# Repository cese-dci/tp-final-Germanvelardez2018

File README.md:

## Trabajo práctico final de la asignatura DCI ##
Este repositorio contiene el trabajo práctico final para la asignatura de Diseño de Circuitos Impresos de la carrera de posgrado de FIUBA.

* Autor: German Gabriel Velardez
* Título corto del trabajo:  Replica de modulo de comunicacion basado en el chip SIM7000G
* Descripción:  Modulo de comunicacion basado GSM/4G con GNSS incluido.

## Licencia de este trabajo ##
La licencia utilizada en este proyecto es : <b>CERN Open Hardware Licence Version 2</b>. 

## Estructura del TP FINAL ##

Se repositorio esta estructurado de la siguiente manera.

* doc: Toda la información sobre el circuito, principalmente de autoría o procesamiento propio. 
* info: Toda la iformación recolectada sobre el circuito, como por ejemplo:
  * Hojas de datos.
  * Info de productos comerciales.
  * Info en internet.
* pcb: Archivos de diseño esquemático y pcb.

## Replica de modulo de comunicacion basado en SIM7000
# Diseño final

 ### Dimensiones del nuevo modulo:
  <ul>
    <li>
     Largo: 80 mm
    </li>  
    <li>
    Ancho: 60 mm
    </li> 
  </lu> 

  ### Primera tentativa de posicionamiento de elementos

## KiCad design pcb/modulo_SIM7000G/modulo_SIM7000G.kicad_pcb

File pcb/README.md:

## Archivos Kicad ##
Este directorio contiene 2 carpetas:
<ul>
  <li>[lib] Librerias de componentes y modelos 3D</li>
  <li>[modulo_SIM7000G] Carpeta del proyecto KICAD</li>
  <ul>

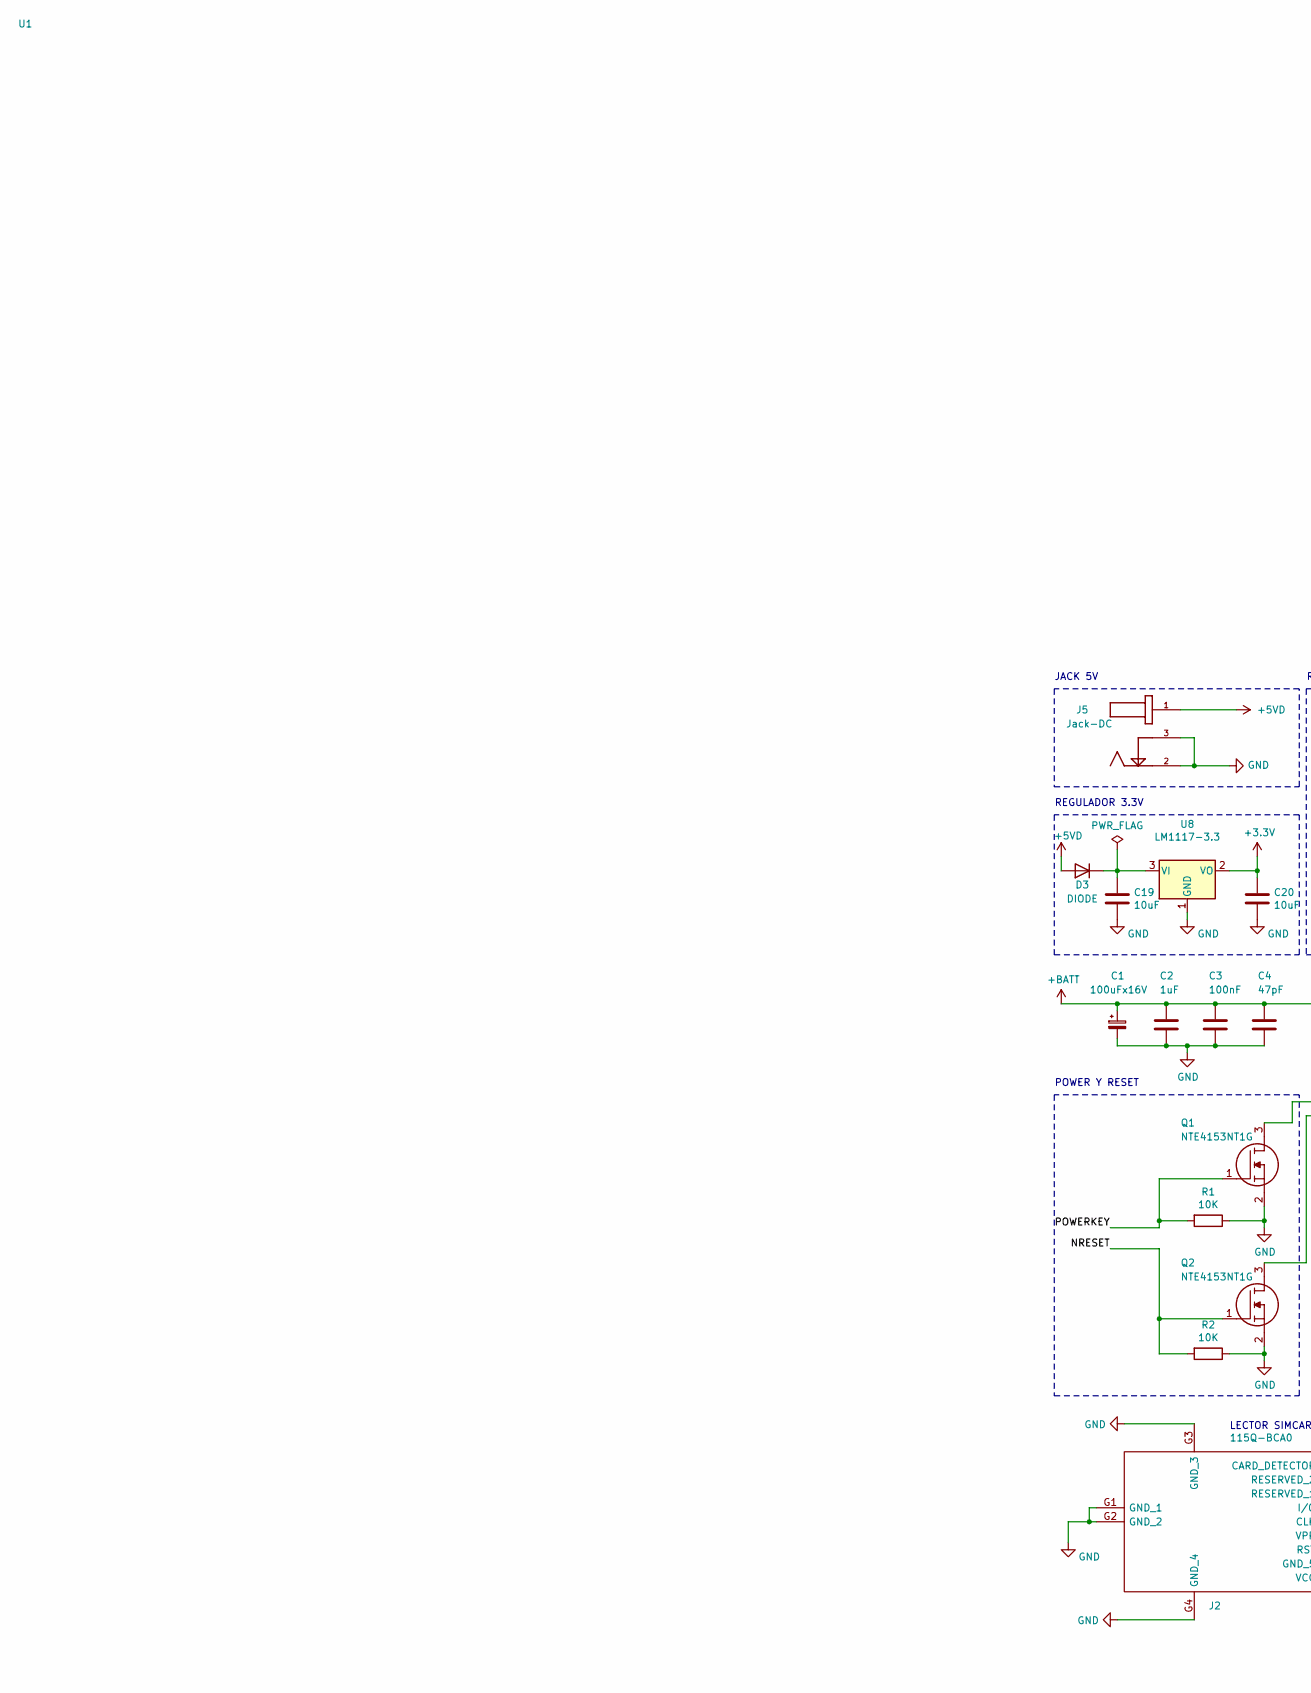
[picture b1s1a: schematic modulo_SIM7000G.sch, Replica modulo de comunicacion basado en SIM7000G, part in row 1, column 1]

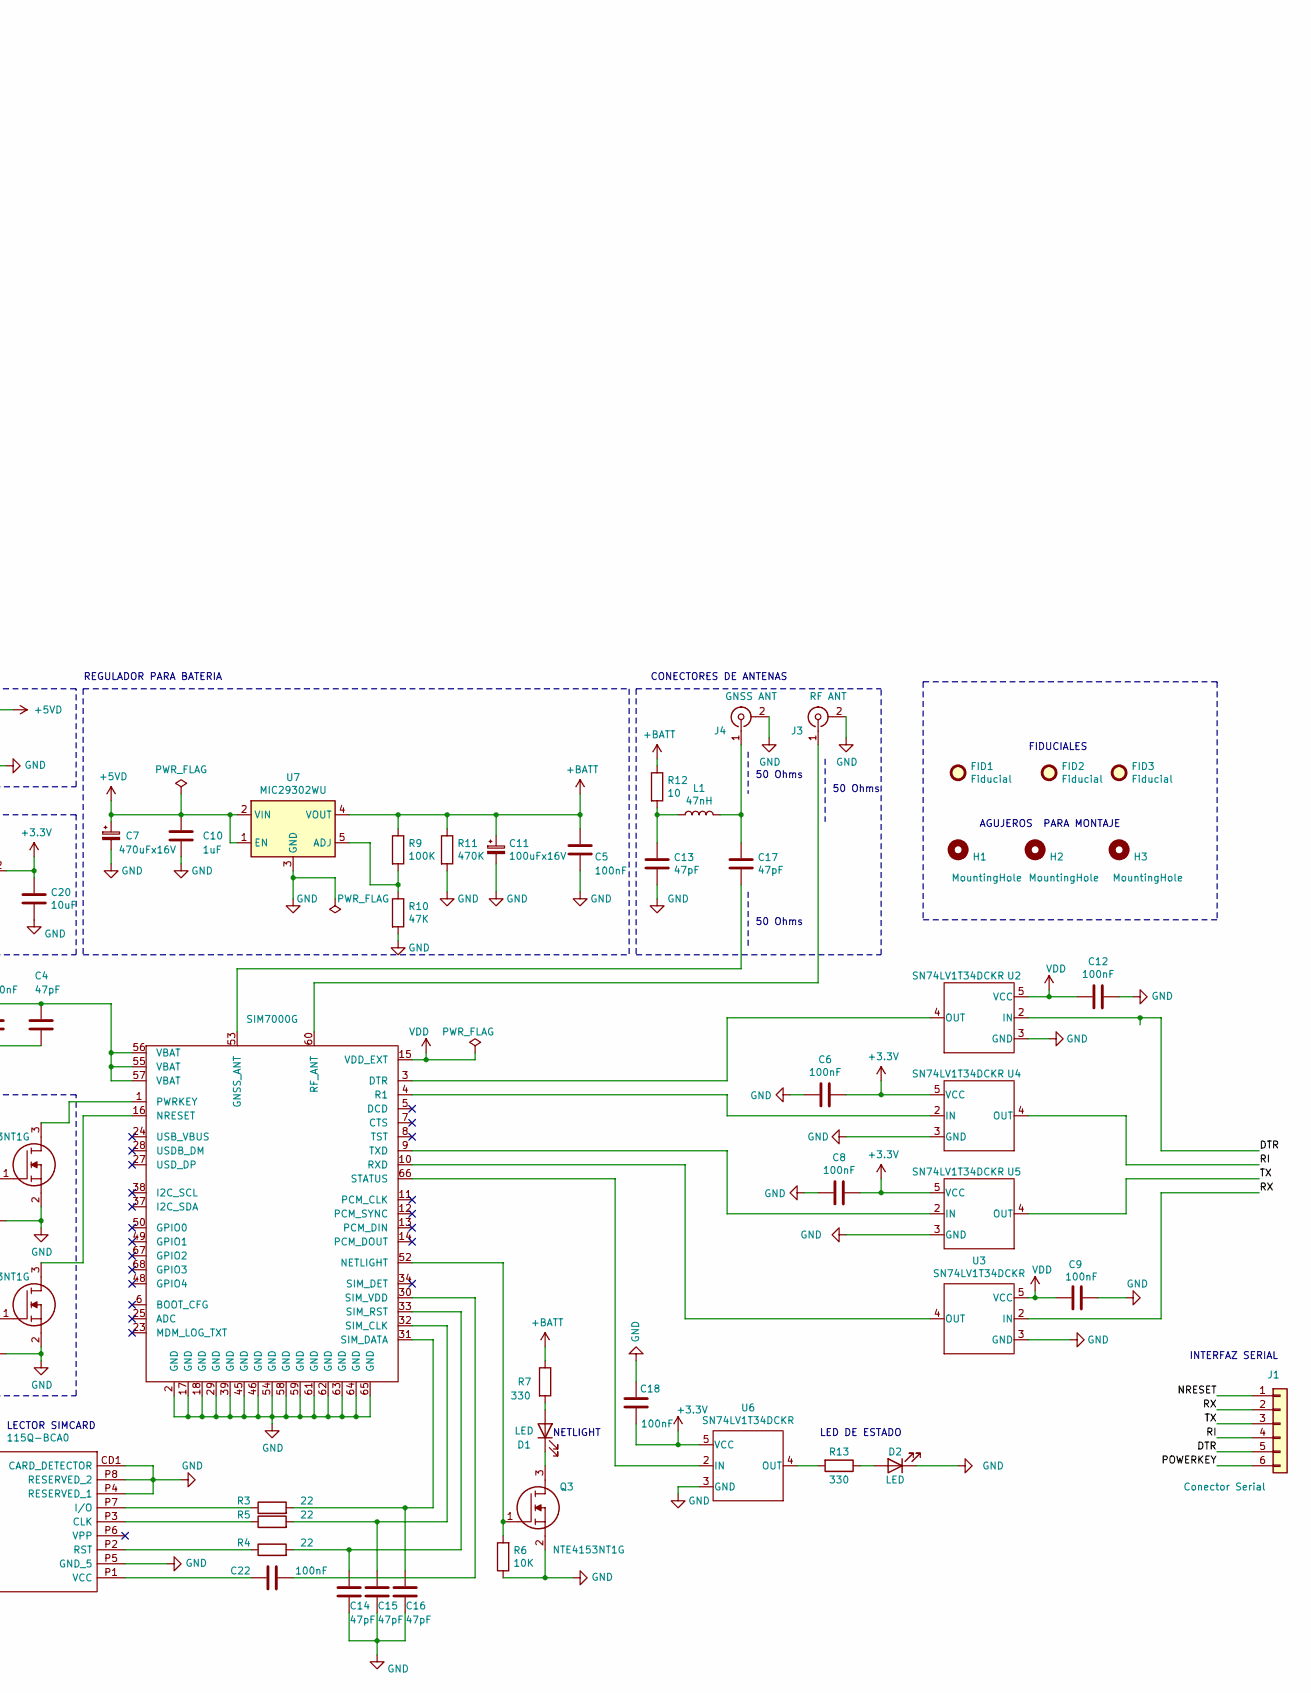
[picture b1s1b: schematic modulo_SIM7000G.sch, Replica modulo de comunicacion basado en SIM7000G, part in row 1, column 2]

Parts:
C1, C11: 100uFx16V; CP_Elec_6.3x9.9
C2, C10: 1uF; C_0805_2012Metric_Pad1.18x1.45mm_HandSolder
C3, C5, C6, C8, C9, C12, C18, C22: 100nF; C_0805_2012Metric_Pad1.18x1.45mm_HandSolder
C4, C13, C14, C15, C16, C17: 47pF; C_0805_2012Metric_Pad1.18x1.45mm_HandSolder
C7: 470uFx16V; CP_Elec_8x10
C19, C20: 10uF; C_0805_2012Metric_Pad1.18x1.45mm_HandSolder
D1, D2: LED; LED_0805_2012Metric
D3: DIODE; D_0805_2012Metric_Pad1.15x1.40mm_HandSolder
FID1, FID2, FID3: Fiducial; Fiducial_1mm_Mask2mm
H1, H2, H3: MountingHole; MountingHole_2.2mm_M2_ISO7380_Pad_TopBottom
J1: Conector Serial; PinHeader_1x06_P2.54mm_Horizontal
J2: 115Q-BCA0; 115QBCA0; Manufacturer_Part_Number 115Q-BCA0
J3: RF ANT; SMA_Amphenol_132203-12_Horizontal
J4: GNSS ANT; SMA_Amphenol_132203-12_Horizontal
J5: Jack-DC; BarrelJack_CUI_PJ-063AH_Horizontal
L1: 47nH; L_0805_2012Metric
Q1, Q2, Q3: NTE4153NT1G; SOT-416; Manufacturer_Part_Number NTE4153NT1G; Mouser Part Number 863-NTE4153NT1G
R1, R2, R6: 10K; R_0805_2012Metric
R3, R4, R5: 22; R_0805_2012Metric
R7, R13: 330; R_0805_2012Metric
R9: 100K; R_0805_2012Metric
R10: 47K; R_0805_2012Metric
R11: 470K; R_0805_2012Metric
R12: 10; R_0805_2012Metric
U1: SIM7000G; SIM7000
U2, U3, U4, U5, U6: SN74LV1T34DCKR; SOT-23-5
U7: MIC29302WU; TO-263-5_TabPin3; Digikey 576-1125-2-NDTR
U8: LM1117-3.3; SOT-223

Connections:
+3V3: C6.2, C8.2, C18.1, C20.1, U4.5 (VCC), U5.5 (VCC), U6.5 (VCC), U8.2 (VO)
+5VD: C7.1, C10.1, D3.1 (A), J5.1, U7.1 (EN), U7.2 (VIN)
+BATT: C1.1, C2.1, C3.1, C4.1, C5.1, C11.1, R7.1, R9.1, R11.1, R12.1, U1.55 (VBAT), U1.56 (VBAT), U1.57 (VBAT), U7.4 (VOUT)
/DTR: J1.5, U2.2 (IN)
/NRESET: J1.1, Q2.1, R2.2
/POWERKEY: J1.6, Q1.1, R1.2
/RI: J1.4, U4.4 (OUT)
/RX: J1.2, U3.2 (IN)
/TX: J1.3, U5.4 (OUT)
GND: C1.2, C2.2, C3.2, C4.2, C5.2, C6.1, C7.2, C8.1, C9.2, C10.2, C11.2, C12.2, C13.2, C14.2, C15.2, C16.2, C18.2, C19.2, C20.2, D2.1 (K), J2.CD1 (CARD_DETECTOR), J2.G1 (GND_1), J2.G2 (GND_2), J2.G3 (GND_3), J2.G4 (GND_4), J2.P4 (RESERVED_1), J2.P5 (GND_5), J2.P8 (RESERVED_2), J3.2 (Ext), J4.2 (Ext), J5.2, J5.3, Q1.2, Q2.2, Q3.2, R1.1, R2.1, R6.1, R10.2, R11.2, U1.2 (GND), U1.17 (GND), U1.18 (GND), U1.29 (GND), U1.39 (GND), U1.45 (GND), U1.46 (GND), U1.54 (GND), U1.58 (GND), U1.59 (GND), U1.61 (GND), U1.62 (GND), U1.63 (GND), U1.64 (GND), U1.65 (GND), U2.3 (GND), U3.3 (GND), U4.3 (GND), U5.3 (GND), U6.3 (GND), U7.3 (GND), U8.1 (GND)
unnamed: C13.1, L1.1, R12.2
unnamed: C14.1, R4.2, U1.33 (SIM_RST)
unnamed: C15.1, R5.2, U1.32 (SIM_CLK)
unnamed: C16.1, R3.2, U1.31 (SIM_DATA)
unnamed: C17.1, J4.1 (In), L1.2
unnamed: C17.2, U1.53 (GNSS_ANT)
unnamed: C19.1, D3.2 (K), U8.3 (VI)
unnamed: C22.1, J2.P1 (VCC)
unnamed: C22.2, U1.30 (SIM_VDD)
unnamed: D1.1 (K), Q3.3
unnamed: D1.2 (A), R7.2
unnamed: D2.2 (A), R13.1
unnamed: J2.P2 (RST), R4.1
unnamed: J2.P3 (CLK), R5.1
unnamed: J2.P7 (I/O), R3.1
unnamed: J3.1 (In), U1.60 (RF_ANT)
unnamed: Q1.3, U1.1 (PWRKEY)
unnamed: Q2.3, U1.16 (NRESET)
unnamed: Q3.1, R6.2, U1.52 (NETLIGHT)
unnamed: R9.2, R10.1, U7.5 (ADJ)
unnamed: R13.2, U6.4 (OUT)
unnamed: U1.3 (DTR), U2.4 (OUT)
unnamed: U1.4 (R1), U4.2 (IN)
unnamed: U1.9 (TXD), U5.2 (IN)
unnamed: U1.10 (RXD), U3.4 (OUT)
unnamed: U1.66 (STATUS), U6.2 (IN)
VDD: C9.1, C12.1, U1.15 (VDD_EXT), U2.5 (VCC), U3.5 (VCC)

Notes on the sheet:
REGULADOR 3.3V
POWER Y RESET
FIDUCIALES
AGUJEROS PARA MONTAJE
JACK 5V
REGULADOR PARA BATERIA
LECTOR SIMCARD
NETLIGHT
LED DE ESTADO
CONECTORES DE ANTENAS
INTERFAZ SERIAL
50 Ohms

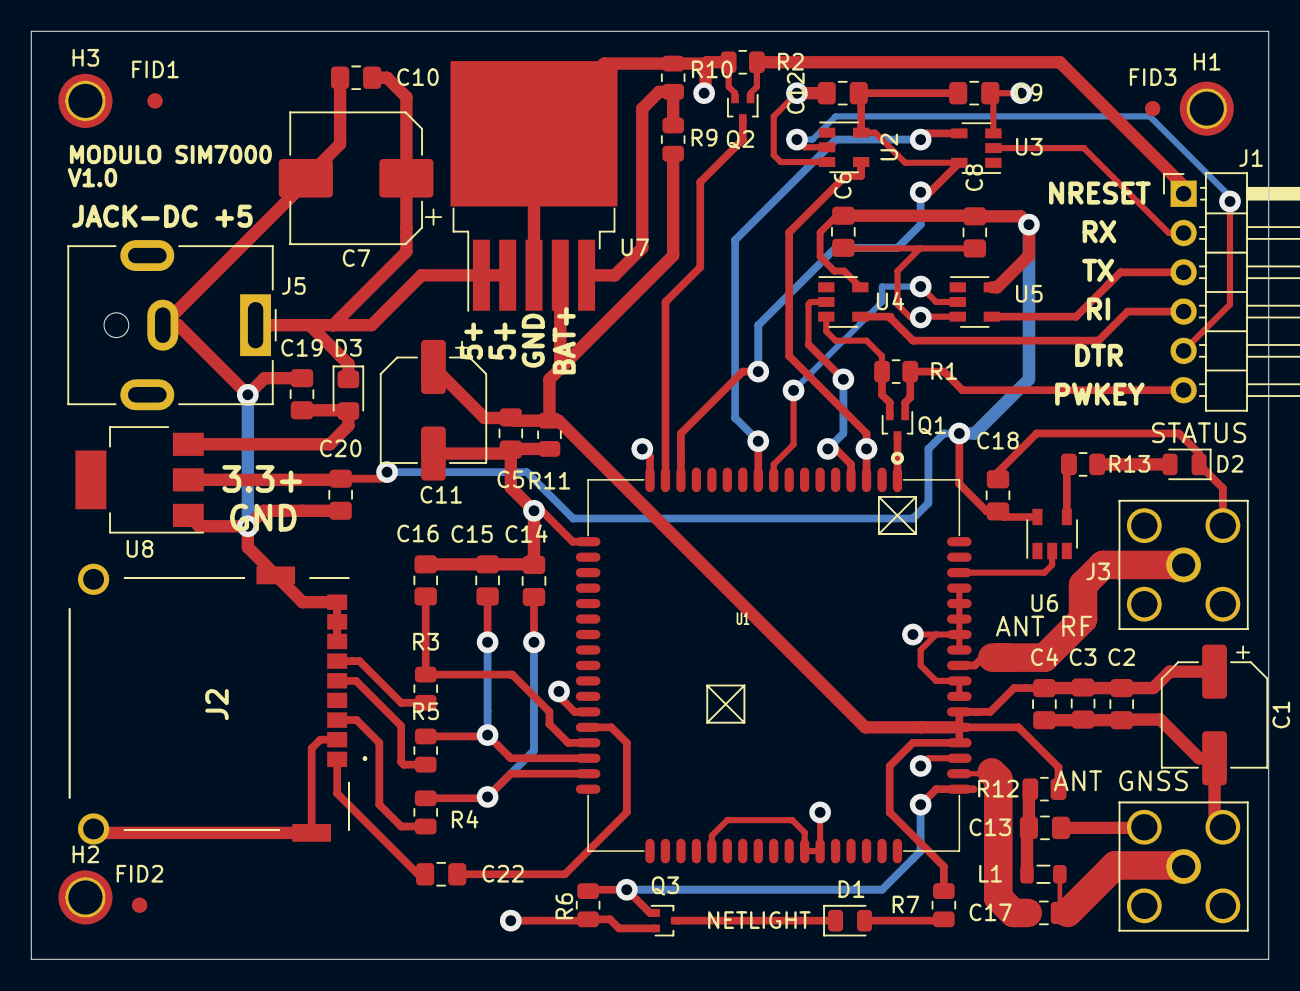
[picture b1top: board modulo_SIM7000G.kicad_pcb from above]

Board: 2 copper layers, 80.0 x 60.0 mm, 59 parts (0 on the bottom side), 37 nets.

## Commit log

2021-09-08 Se Completado datos en el readme
2021-09-08 Se agrego licencia
2021-09-08 Se agrego esquematico del sistema
2021-09-08 modificaciones al readme
2021-09-08 Avances en el esquematico del circuito
2021-09-14 avances en el esquematico(casi terminado) consultar detalles sobre como poner referencias a USB33, VBAT, VEXT, ect
2021-09-14 mejora en el esquematico
2021-09-14 avance en el esquematico, se posiciono todos los componentes, solo falta agregar VBAT, V5EXT y otras referencia de tension donde corresponda
2021-09-16 se agregaron valores a componentes
2021-09-22 Modificaciones en el esquematico, se agrego un conector lector de sim modelo 115Q-BCA0
2021-09-22 agregando archivos en carpeta propuesta
2021-09-22 se agrego imagen de posicionmiento tentativo
2021-09-22 Acomodando archivos y carpetas del repo
2021-09-22 Se agrego connectores de antenas
2021-09-22 se mejoror imagen de posicionamiento tentativo
2021-09-22 modificaciones en el readme de propuesta
2021-09-22 Se generaron los archivos de asignacion de huellas y figuras 3d
2021-09-24 correciones en el esquematico, se agrego agujeros de montaje
2021-09-29 antes de empezar el diseño de las pistas
2021-10-07 se termino de diseñar las pistas. Falta plano de alimentacion y detalles
2021-10-07 pcb terminado.
2021-10-08 modificaciones en reglas de diseño del proyecto
2021-10-12 antes de realizar modificaciones rf
2021-10-13 termine, falta los modelos 3d de los conectores.
2021-10-13 se redujo el tamaño de el pcb de 100x60 a 80x 60
2021-10-14 Se agrego los conectores de antenas. Faltasolucionar tema rutas relativas
2021-10-14 conectando nodos
2021-10-14 todo listo, menos el tema de las rutas relativas
2021-10-14 se agrego imagen del diseño final

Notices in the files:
pcb/modulo_SIM7000G/modulo_SIM7000G.kicad_pcb:
Licencia: CERN Open Hardware Licence Version 2.
